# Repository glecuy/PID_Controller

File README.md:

## Universal motor PID speed regulator for bench drill.

ATMEGA 328 based DC motor electronic regulator.

It uses pms67/PID library (https://github.com/pms67/PID)

# Hardware design
  - A potentiometer is used at input to select desired speed.
  - Actual speed is measured and sent to controller
  - ATmega microcontroller compute resulting PWM signal
  - A MOSFET modulates MOTOR DC voltage.
  - Switching frequency is 32KHz.

# Software design
  - Potentiometer position is read via ADC3 (setpoint)
  - Speed sensor connected to INT0 and measured by counting timer2 ticks (measurement)
  - Sampling rate is set to 0.1 Sec and call to PIDController_Update()
  - Output is used to control motor voltage (PWM)
  - Calculations are done in floating point and normalized to one.

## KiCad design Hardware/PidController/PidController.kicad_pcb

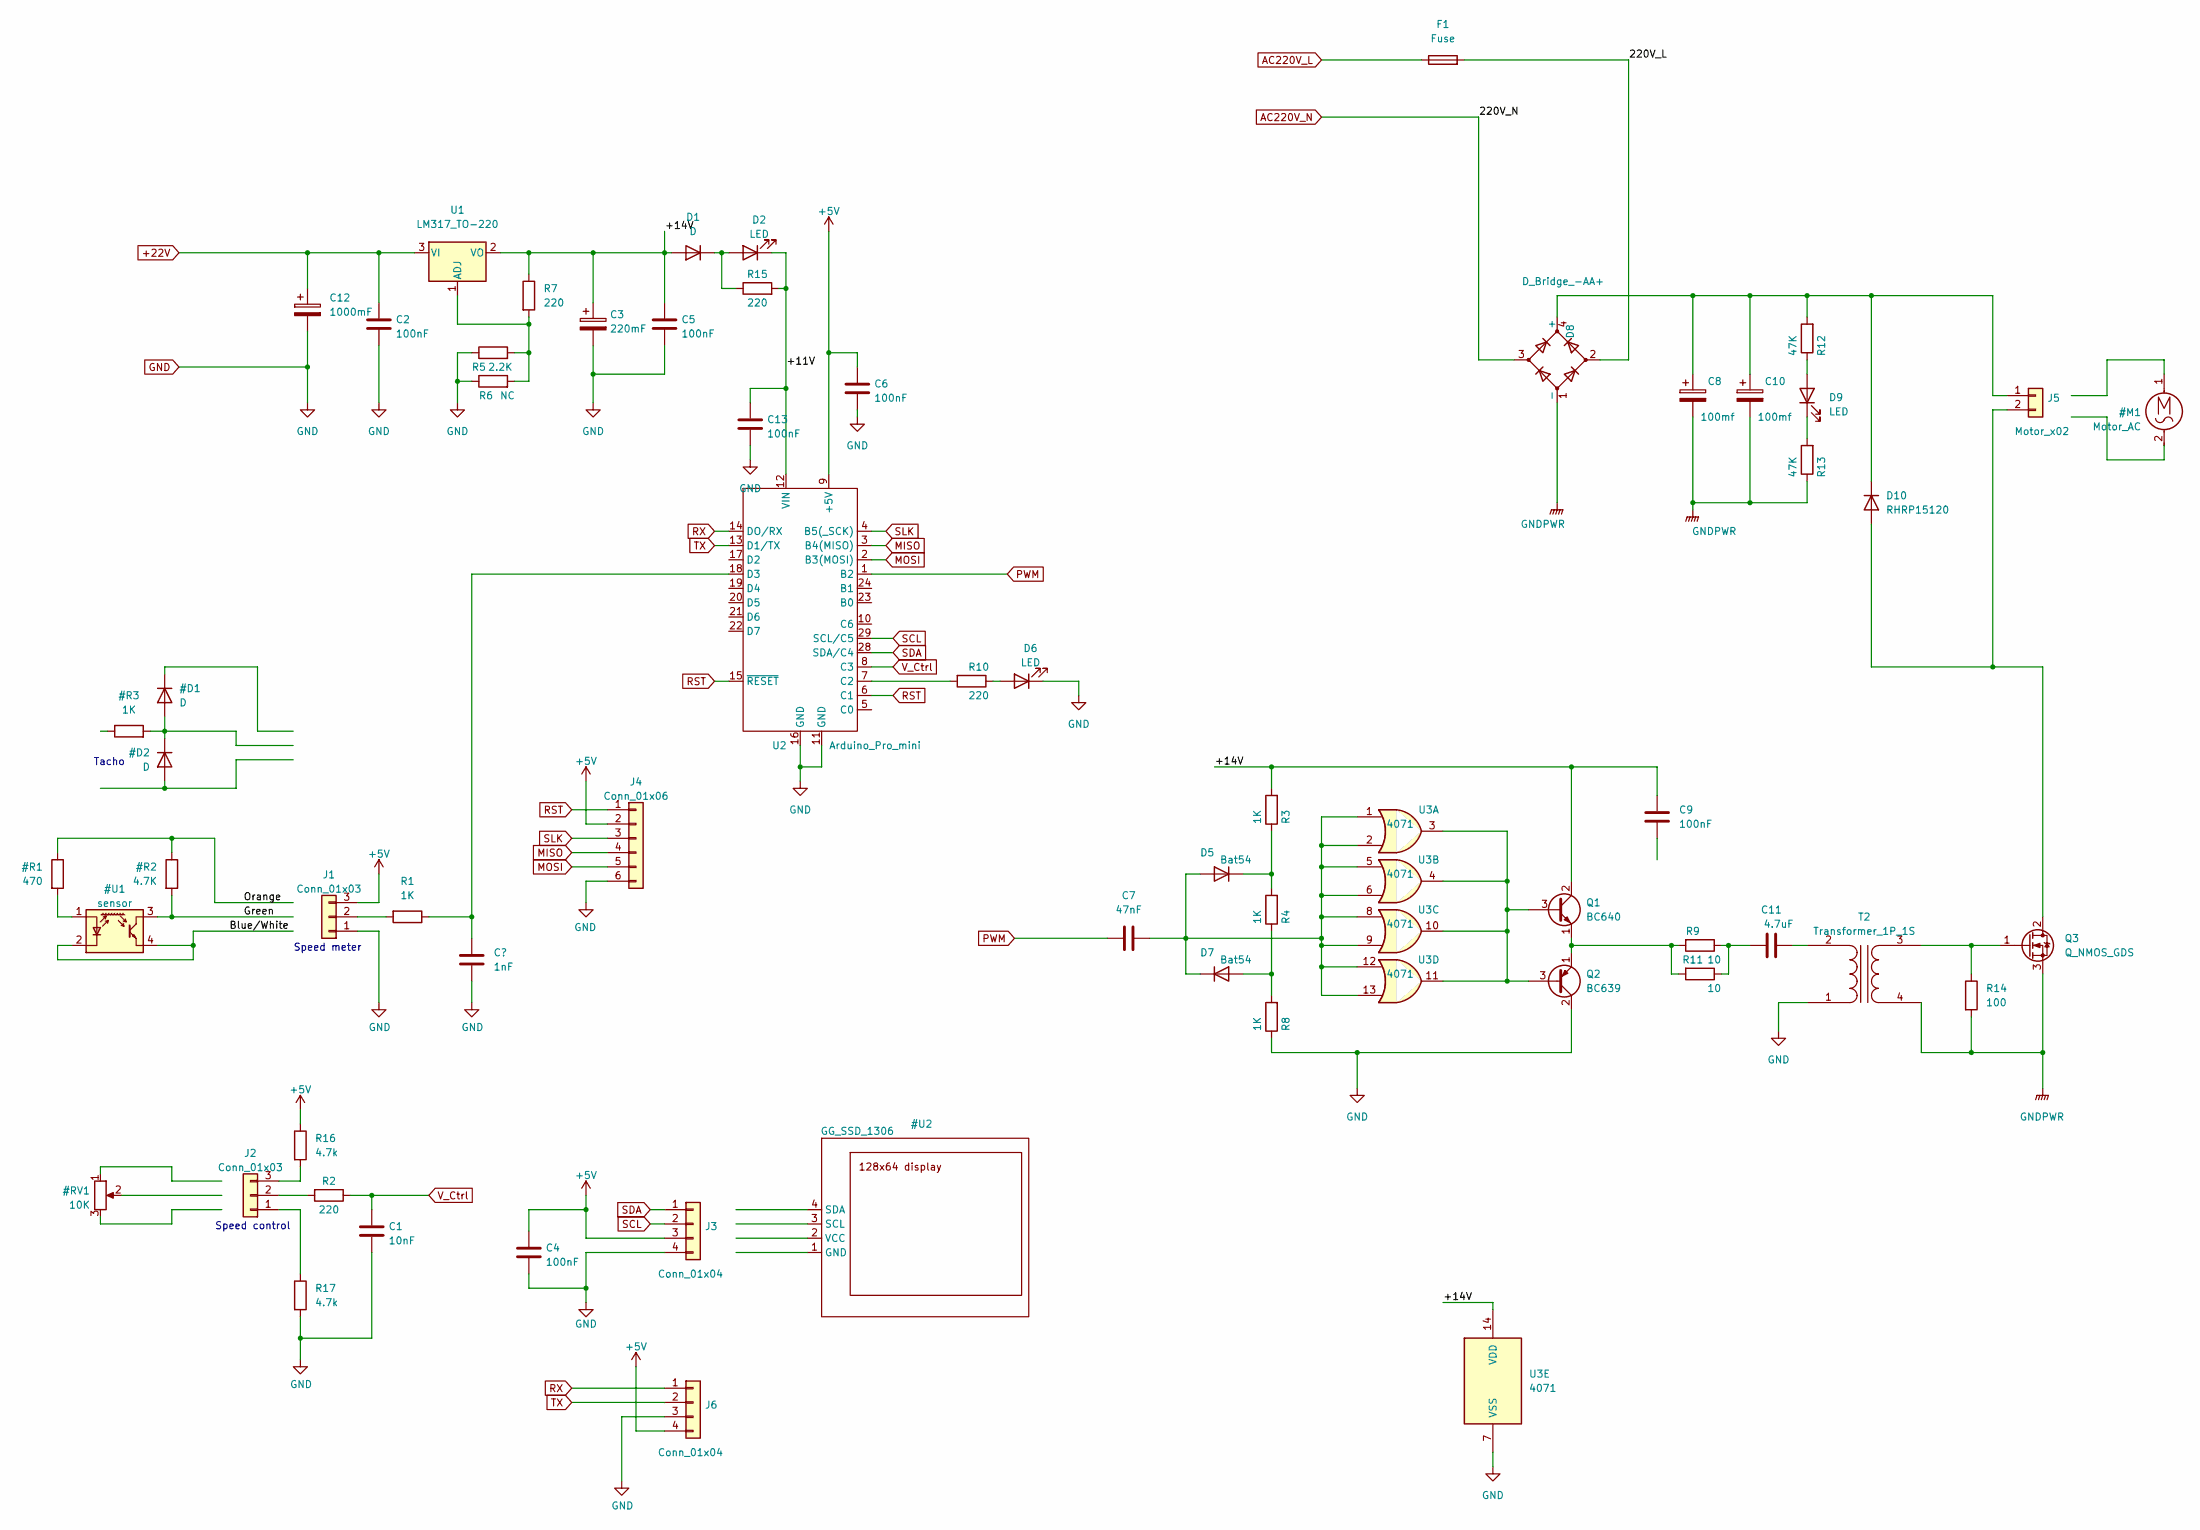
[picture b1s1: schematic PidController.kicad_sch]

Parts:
C1: 10nF; C_0805_2012Metric_Pad1.18x1.45mm_HandSolder
C2, C5: 100nF; LED_1210_3225Metric
C3: 220mF; CP_Radial_D8.0mm_P5.00mm
C4, C6, C9, C13: 100nF; C_0805_2012Metric_Pad1.18x1.45mm_HandSolder
C7: 47nF; C_0805_2012Metric_Pad1.18x1.45mm_HandSolder
C8, C10: 100mf; CP_Radial_D18.0mm_P7.50mm
C11: 4.7uF; C_Film_5.08
C12: 1000mF; CP_Radial_D8.0mm_P5.00mm
D1: D; D_5KPW_P12.70mm_Horizontal
D2, D6: LED; LED_2010_5025Metric
D5, D7: Bat54; D_SOT-23_ANK
D8: D_Bridge_-AA+; Diode_Bridge_300V
D9: LED; LED_1210_3225Metric_Pad1.42x2.65mm_HandSolder
D10: RHRP15120; D_TO-220-2_Vertical
F1: Fuse; Fuse_5X20
J1: Conn_01x03; GG_PinHeader_1x03
J2: Conn_01x03; JWT_1x03_P3.96mm_Vertical
J3, J6: Conn_01x04; GG_PinHeader_1x04
J4: Conn_01x06; GG_PinHeader_1x06
J5: Motor_x02; MotorConnector_2
Q1: BC640; TO-92_delta
Q2: BC639; TO-92_delta
Q3: Q_NMOS_GDS; TO-247-3_Vertical
R1, R3, R4, R8: 1K; R_1206_3216Metric_Pad1.30x1.75mm_HandSolder
R2, R7, R10, R15: 220; R_1206_3216Metric_Pad1.30x1.75mm_HandSolder
R5: 2.2K; R_1206_3216Metric_Pad1.30x1.75mm_HandSolder
R6: NC; R_1206_3216Metric_Pad1.30x1.75mm_HandSolder
R9, R11: 10; R_1206_3216Metric_Pad1.30x1.75mm_HandSolder
R12, R13: 47K; R_1206_3216Metric_Pad1.30x1.75mm_HandSolder
R14: 100; R_Axial_DIN0309_L9.0mm_D3.2mm_P12.70mm_Horizontal
R16, R17: 4.7k; R_1206_3216Metric_Pad1.30x1.75mm_HandSolder
T2: Transformer_1P_1S; Transformer_Toroid_Horizontal_D18.0mm
U1: LM317_TO-220; TO-263-2
U2: Arduino_Pro_mini; GG_Arduino_Pro_MiniEVB
U3: 4071; DIP-14_W8.89mm_SMDSocket_LongPads

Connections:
+5V: C4.1, C6.1, J1.3, J3.3, J4.2, J6.4, R16.1, U2.9 (+5V)
+22V: C2.1, C12.1, U1.3 (VI)
/220V_L: D8.2, F1.2
/+11V: C13.1, D2.1 (K), R15.2, U2.12 (VIN)
/+14V: C3.1, C5.1, C9.2, D1.2 (A), Q1.2 (C), R3.2, R7.1, U1.2 (VO), U3.14 (VDD)
AC220V_L: F1.1
AC220V_N: D8.3
GND: C1.2, C2.2, C3.2, C4.2, C5.2, C6.2, C12.2, C13.2, D6.1 (K), J1.1, J3.4, J4.6, J6.3, Q2.2 (C), R5.1, R6.1, R8.1, R17.2, T2.1 (AA), U2.11 (GND), U2.16 (GND), U3.7 (VSS)
GNDPWR: C8.2, C10.2, D8.1 (-), Q3.3 (S), R13.1, R14.2, T2.4 (SB)
MISO: J4.4, U2.3 (B4(MISO))
MOSI: J4.5, U2.2 (B3(MOSI))
unnamed: C7.2, D5.2 (A), D7.1 (K), U3.1, U3.2, U3.5, U3.6, U3.8, U3.9, U3.12, U3.13
unnamed: C8.1, C10.1, D8.4 (+), D10.1 (K), J5.1, R12.2
unnamed: C11.1, R9.1, R11.1
unnamed: C11.2, T2.2 (AB)
unnamed: D1.1 (K), D2.2 (A), R15.1
unnamed: D5.1 (K), R3.1, R4.2
unnamed: D6.2 (A), R10.1
unnamed: D7.2 (A), R4.1, R8.2
unnamed: D9.1 (K), R13.2
unnamed: D9.2 (A), R12.1
unnamed: D10.2 (A), J5.2, Q3.2 (D)
unnamed: J1.2, R1.2
unnamed: J2.1, R17.1
unnamed: J2.2, R2.2
unnamed: J2.3, R16.2
unnamed: Q1.1 (E), Q2.1 (E), R9.2, R11.2
unnamed: Q1.3 (B), Q2.3 (B), U3.3, U3.4, U3.10, U3.11
unnamed: Q3.1 (G), R14.1, T2.3 (SA)
unnamed: R1.1, U2.18 (D3)
unnamed: R5.2, R6.2, R7.2, U1.1 (ADJ)
unnamed: R10.2, U2.7 (C2)
PWM: C7.1, U2.1 (B2)
RST: J4.1, U2.6 (C1), U2.15 (~RESET)
RX: J6.1, U2.14 (DO/RX)
SCL: J3.2, U2.29 (SCL/C5)
SDA: J3.1, U2.28 (SDA/C4)
SLK: J4.3, U2.4 (B5(_SCK))
TX: J6.2, U2.13 (D1/TX)
V_Ctrl: C1.1, R2.1, U2.8 (C3)

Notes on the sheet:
Tacho
Speed control
Speed meter

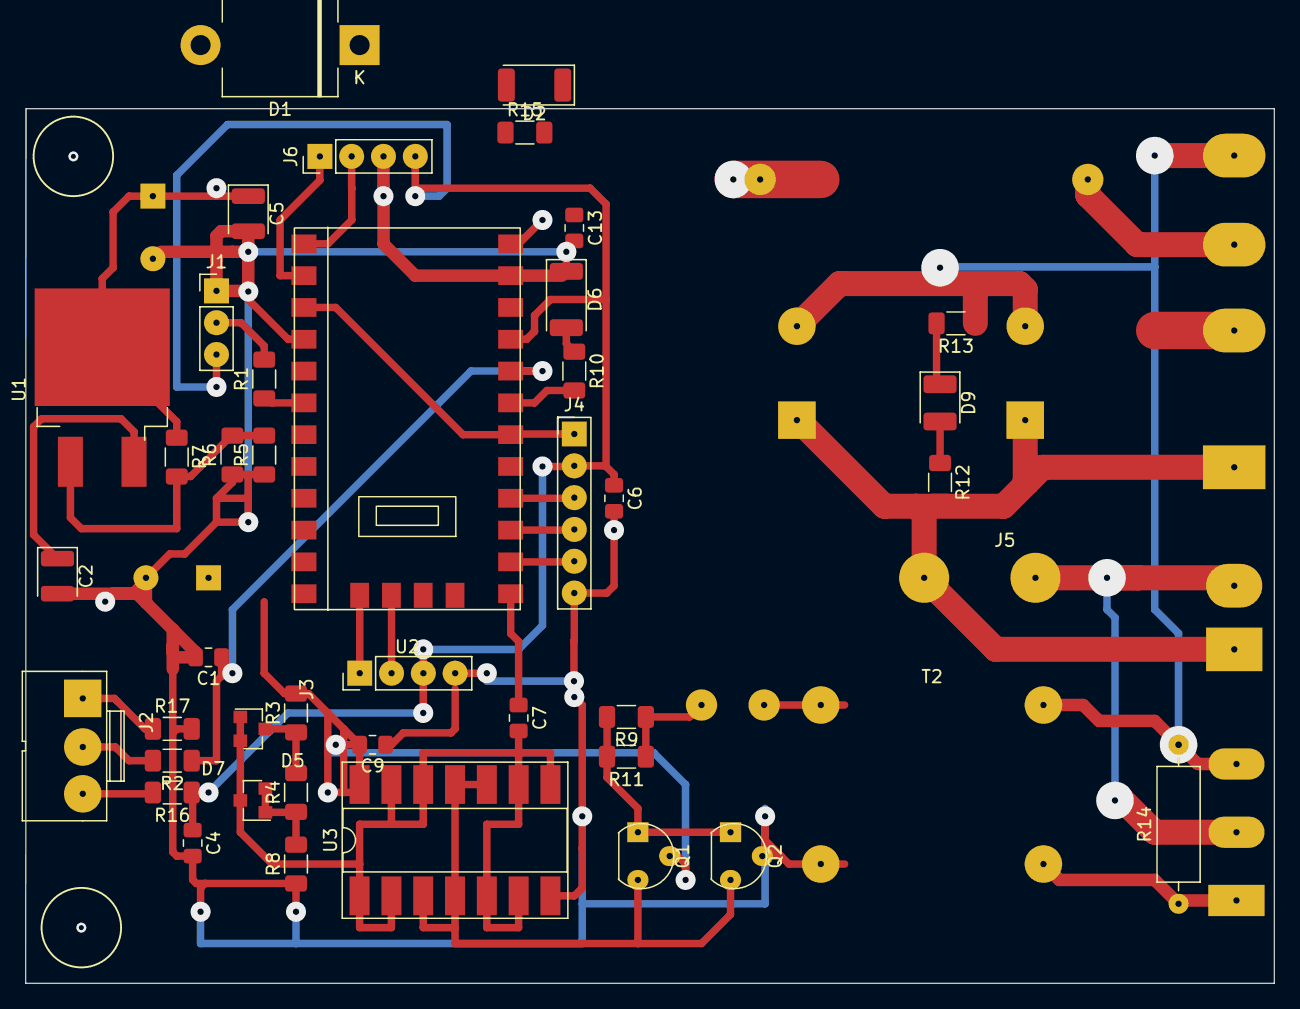
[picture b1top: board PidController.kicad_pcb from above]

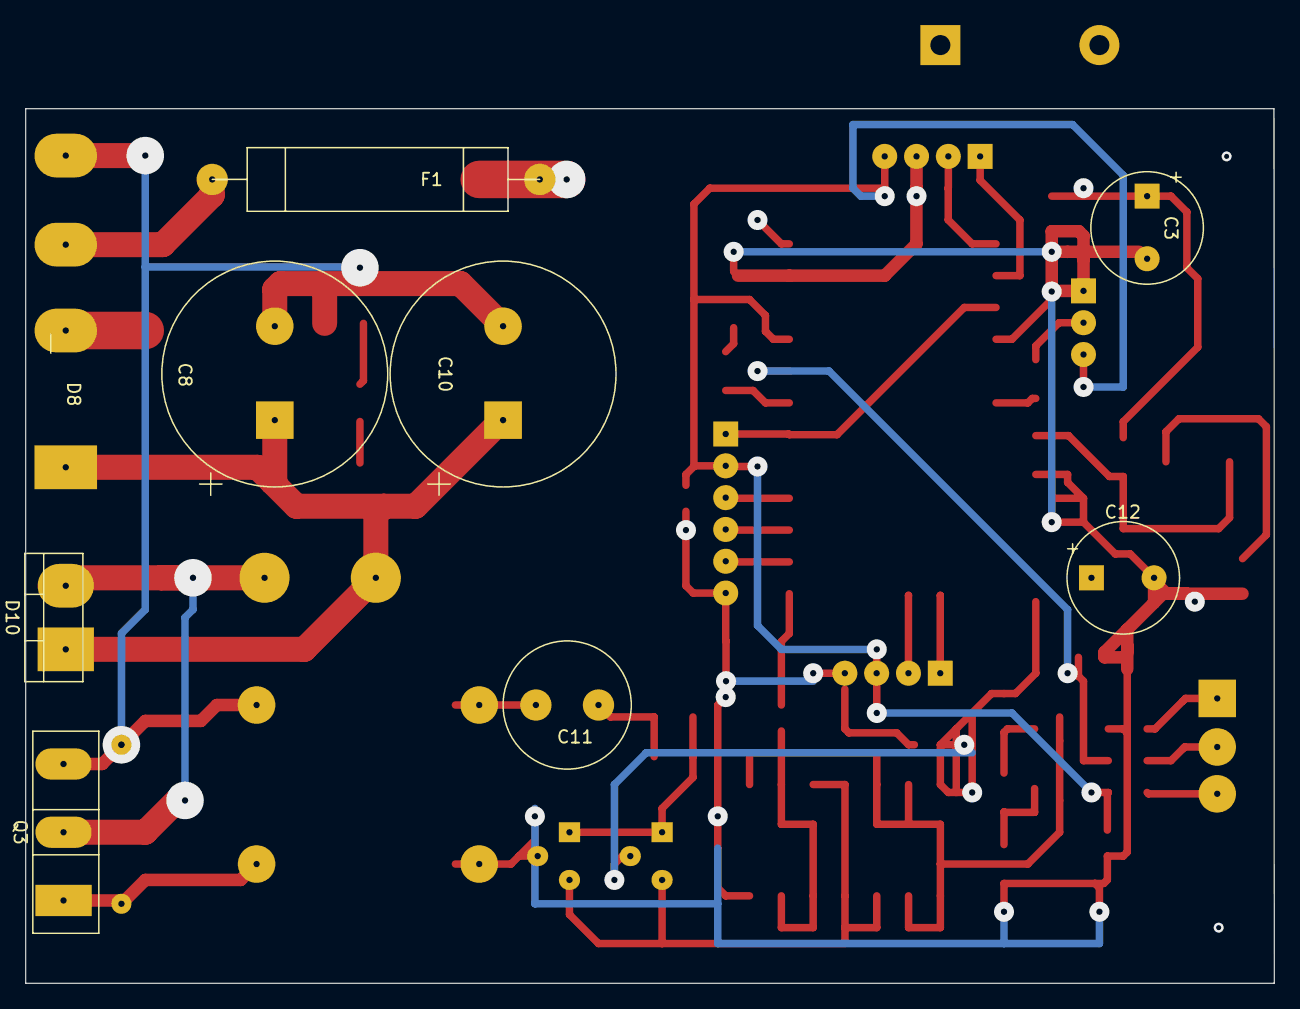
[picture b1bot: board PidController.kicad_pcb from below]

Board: 2 copper layers, 99.7 x 69.8 mm, 52 parts (9 on the bottom side), 38 nets.

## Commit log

2025-06-12 Initial commit, Triac control tested
2025-06-12 Add motor simulator
2025-06-12 Integrate PID code from pms67/PID package
2025-06-12 First tests done, first PID params tuning
2025-06-12 Improve PID parameters with bench drill
2025-06-12 Update README text
